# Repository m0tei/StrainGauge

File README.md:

# Strain Gauge Amplifier

A very small analog amplifier board for a full-bridge strain gauge on a carbon rod. It powers the bridge, amplifies the tiny bridge signal by about 151, filters it, and sends one analog voltage to an ADC.

| | |
|---|---|
| Board size | 18.35 × 5.0 mm, 0.8 mm thick, 2 layers |
| Supply | 5 V in, 3.3 V on board |
| Output | Analog, 0.825 V at zero strain |
| Sensitivity | About 0.649 mV/µε at the output |
| Usable range | About 3730 µε compression, 1190 µε extension |
| Bandwidth | About 480 Hz |
| Bridge | 350 Ω full bridge, 3.3 V excitation |
| Design tool | KiCad 10 |

Sensitivity and range assume a gauge factor of 2 and a Poisson ratio of 0.3. Replace these with your gauge and rod values when calibrating.

> **Status:** this is a design that passes KiCad's electrical and layout checks. This repository has no test results from a built board. See [Before ordering](#before-ordering).

## The board

**Top side:** amplifier U2, regulator U1, input filter, and ferrites. The gauge pads J2 are on the left and the cable pads J1 are on the right.

**Bottom side:** VREF buffer U3, VREF divider RN1, gain resistors R1 and R2, output filter R4 and C5, and ESD diodes D1 and D2. This view is flipped, so J2 is on the right.

## How it works

```mermaid
flowchart LR
    A[5 V from J1] --> B[FB1 and D1]
    B --> C[U1 3.3 V regulator]
    C --> D[Strain gauge bridge]
    C --> E[RN1 and U3 make 0.825 V VREF]
    D --> F[Input filter]
    F --> G[U2 amplifier, gain 151]
    E --> G
    G --> H[R4 and C5 output filter]
    H --> I[FB2 and D2]
    I --> J[OUT on J1]
```

### 1. The bridge

Four 350 Ω gauges are bonded to the rod. SG1 and SG3 are axial and sit on opposite sides of the rod. SG2 and SG4 are transverse.

Bending affects the two axial gauges in opposite directions, so it largely cancels. Pure tension or compression adds up. With a 3.3 V supply, the bridge gives about 4.3 µV for each microstrain.

### 2. Power

The 5 V input passes through ferrite FB1, which keeps high-frequency noise out of the regulator. D1 clamps spikes from the cable.

U1 (TPS7A2033) makes the 3.3 V rail. It powers the amplifier and the bridge, and it is also the source for VREF. The bridge draws about 9.4 mA.

### 3. Mid-supply reference

RN1 is a 10k/30k pair that divides 3.3 V by four, and U3 buffers it to make a low-impedance 0.825 V **VREF**. This sets the amplifier's zero point. It sits low because the expected load is lopsided: 3000 µε compression and 300 µε extension. Compression drives the output up, and extension drives it down.

### 4. Input filter

R5, R6, and C6 form a differential low-pass filter with a corner of about 29 kHz, including the bridge resistance. It reduces high-frequency interference picked up on the gauge wires.

### 5. Amplifier

U2 (MCP6N16-100) is a zero-drift instrumentation amplifier. Zero drift means it constantly corrects its own offset, which suits slow, tiny signals like this one.

Two external resistors set the gain:

```
Gain = 1 + R2 / R1 = 1 + 100k / 665 = 151.4
```

The gain depends on the **ratio** of R2 to R1, not their absolute values. R1 is rated ±5 ppm/K and R2 ±10 ppm/K. They come from the same Susumu RG1005 range and sit next to each other, so their ratio stays stable as temperature changes.

The output is:

```
VOUT = VREF + Gain × (SIG+ − SIG−)
```

### 6. Output

R4 and C5 form a low-pass filter at about 480 Hz. This removes noise above the signal band and isolates the amplifier from the cable. FB2 and D2 add high-frequency blocking and ESD protection at the output.

## Wiring

Use the labels printed on the board, because the J2 pad order is not the same as its pin numbers.

**J2, gauge bridge (top to bottom on the board):**

| Label | Pin | Connects to |
|---|---|---|
| EXC+ | 1 | Bridge top, 3.3 V |
| SIG− | 3 | Junction of SG4 and SG3 |
| SIG+ | 2 | Junction of SG1 and SG2 |
| EXC− | 4 | Bridge bottom, GND |

**J1, cable to the ADC (top to bottom on the board):**

| Signal | Pin | Notes |
|---|---|---|
| OUT | 2 | Analog output |
| +5V | 1 | Power input |
| GND | 3 | Ground |

The `OUT 5V GND` silk label is on the back of the board near J2, not beside J1. Follow the table above when wiring J1.

## Reading the output

Convert the voltage to strain with the line below, where compression is positive:

```
strain (µε) = (VOUT − 0.825 V) / 0.000649 V per µε
```

Treat this as a starting point. For real measurements, calibrate the board on the rod with known loads, and measure the zero point at no load.

Both the zero point and the sensitivity follow the 3.3 V rail, and the ADC cannot see that rail through J1. See the first item below.

## Known limitations

- **3.3 V rail drift:** U1 is rated at ±1.5% over temperature. That could move the zero by up to about 12 mV, or roughly 19 µε. This is the largest temperature error in the design.
- **Gauge wires:** J2 has no ESD diodes and no common-mode filter. EXC+ connects directly to the 3.3 V rail.
- **Chopping frequency:** U2 chops at 25 kHz. Strong interference near that frequency, such as from a motor inverter, could mix down into the signal band.
- **ESD diode position:** D1 and D2 sit after the ferrites, and D2 is about 9 mm from J1. Normally they would sit right at the connector.
- **Automotive qualification:** U1 is not AEC-Q100, and the U2 data sheet makes no AEC-Q100 claim.

## Before ordering

- [ ] Confirm R2's AEC-Q200 status and tempco in the Susumu data sheet.
- [ ] Check stock and lead time for R1 and R2. R1 was listed as not stocked at Digi-Key, with a 22-week lead time.
- [ ] Confirm RN1 can be bought. ACASN1002U3002P1AT follows the Vishay part number scheme, but no distributor listing was found. ACASN1002S3002P1AT is listed and has wider ±15 ppm/K tracking.
- [ ] Tell the assembler that RN1 is now polarized. Pin 1 is the GND pad and the 10k side, marked by a dot on the back silkscreen. Fitted backwards, VREF is 2.475 V.
- [ ] Compare U2's land pattern with Microchip's MSOP-8 package drawing. It was adapted from a VSSOP footprint.
- [ ] Check spacing around U1 with your assembler. Parts are close, and the 5 V link beside FB1 is at the 0.127 mm minimum track width.
- [ ] Review the vias at (115.0, 102.72) and (115.0, 104.48), which sit in or at the edge of pads.

## Bill of materials

The full list with manufacturers, ratings, and sources is in [StrainGauge_BOM.csv](StrainGauge_BOM.csv).

| Ref | Part | Purpose |
|---|---|---|
| U1 | TI TPS7A2033PDBVR | 3.3 V regulator |
| U2 | Microchip MCP6N16-100E/MS | Zero-drift instrumentation amplifier |
| U3 | TI OPA388QDBVRQ1 | VREF buffer |
| R1 | Susumu RG1005V-6650-P-T1, 665 Ω | Gain setting |
| R2 | Susumu RG1005N-104-W-T1, 100 kΩ | Gain setting |
| RN1 | Vishay ACASN1002U3002P1AT, 10k/30k | VREF divider |
| R4 | 1 kΩ | Output filter |
| R5, R6 | 100 Ω | Input filter |
| C1, C2 | 1 µF | Regulator input and output |
| C3, C4, C7 | 100 nF | Decoupling and VREF filtering |
| C5 | 330 nF | Output filter |
| C6 | 10 nF | Input filter |
| FB1, FB2 | Murata BLM15PX601SH1D | Connector EMI filtering |
| D1, D2 | TI TPD1E10B06QDPYRQ1 | ESD protection |

## Files

| File | Contents |
|---|---|
| `StrainGauge.kicad_pro` | KiCad project, open this first |
| `StrainGauge.kicad_sch` | Schematic |
| `StrainGauge.kicad_pcb` | PCB layout |
| `StrainGauge.kicad_sym` | Project symbols |
| `StrainGauge.pretty/` | Project footprints |
| `StrainGauge_BOM.csv` | Bill of materials |
| `StrainGauge_top.png`, `StrainGauge_bottom.png` | Board renders |
| `docs/` | Schematic images used in this README |

## Data sheets

- [MCP6N16 amplifier](https://ww1.microchip.com/downloads/en/DeviceDoc/20005318A.pdf)
- [TPS7A20 regulator](https://www.ti.com/lit/ds/symlink/tps7a20.pdf)
- [ACAS resistor arrays](https://www.vishay.com/doc?28770)

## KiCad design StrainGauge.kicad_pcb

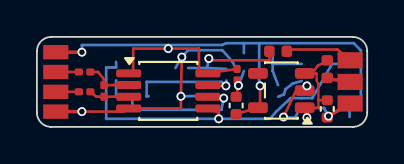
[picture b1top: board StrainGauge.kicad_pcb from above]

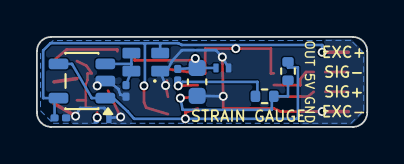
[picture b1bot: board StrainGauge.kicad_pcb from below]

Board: 2 copper layers, 18.3 x 5.0 mm, 22 parts (10 on the bottom side), 14 nets.

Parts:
C1, C2: 1u 10V; C_0402_1005Metric
C3, C4, C7: 100n 10V; C_0201_0603Metric
C5: 330n 16V; C_0603_1608Metric
C6: 10n 10V; C_0201_0603Metric
D1, D2: ESD 5.5V; TVS_X1SON-2_DPY
FB1, FB2: 600R; L_0402_1005Metric
J1: To ADC / 5 V; CablePads_1x03
J2: To rod; GaugePads_1x04
R1: 665R 0.02%; R_0402_1005Metric
R2: 100k 0.05%; R_0402_1005Metric
R4: 1k; R_0201_0603Metric
R5, R6: 100R; R_0201_0603Metric
RN1: 10k/30k; ACAS_0606
U1: TPS7A2033PDBVR; TI_DBV0005A_SOT-23-5
U2: MCP6N16-100E/MS; Microchip_MS_MSOP-8
U3: OPA388QDBVRQ1; TI_DBV0005A_SOT-23-5

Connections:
+3V3: C2.1, C3.1, C7.1, J2.1, RN1.2, U1.5 (OUT), U2.1, U2.8, U3.5
+5V: C1.1, D1.2, FB1.1, U1.1 (IN), U1.3 (EN)
/OUT: C5.1, D2.2, FB2.1, R4.2
/OUT_J1: FB2.2, J1.2
/SIG+: J2.2, R5.1
/SIG-: J2.3, R6.1
/VDIV: C4.1, RN1.3, RN1.4, U3.3
/VFG: R1.1, R2.2, U2.6
/VIN_J1: FB1.2, J1.1
/VO: R2.1, R4.1, U2.7
/VREF: R1.2, U2.5, U3.1, U3.4
GND: C1.2, C2.2, C3.2, C4.2, C5.2, C7.2, D1.1, D2.1, J1.3, J2.4, RN1.1, U1.2 (GND), U2.4, U3.2
unnamed: C6.2, R6.2, U2.2
unnamed: C6.1, R5.2, U2.3

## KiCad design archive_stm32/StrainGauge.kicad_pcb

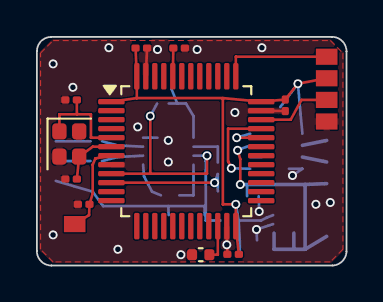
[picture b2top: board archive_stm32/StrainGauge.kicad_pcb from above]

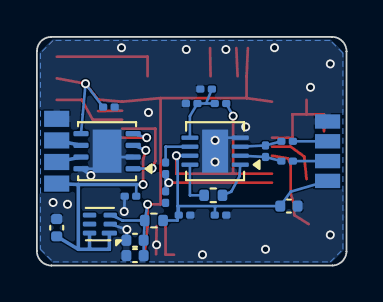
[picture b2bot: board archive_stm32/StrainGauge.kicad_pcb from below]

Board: 2 copper layers, 17.2 x 12.7 mm, 34 parts (23 on the bottom side), 24 nets.

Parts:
C1, C2, C7: 1u 10V; C_0402_1005Metric
C3, C4, C8, C10, C11, C12, C16, C17, C20: 100n; C_0201_0603Metric
C5: 330n; C_0201_0603Metric
C6: 10n; C_0201_0603Metric
C13, C14: 4.7u 10V; C_0402_1005Metric
C18, C19: 10p; C_0201_0603Metric
FB1: 600R 100MHz; R_0402_1005Metric
J1: 5 V / CAN; BusPads_1x04
J2: To rod; GaugePads_1x04
J3: SWD; DebugPads_1x05
R1: 499R 0.1%; R_0402_1005Metric
R2, R3, R4: 1k; R_0201_0603Metric
R5, R6: 100R; R_0201_0603Metric
R7: 10k; R_0201_0603Metric
U1: TLV70033DSE; WSON-6_1.5x1.5mm_P0.5mm
U2: INA333xxDRG; WSON-8-1EP_3x3mm_P0.5mm_EP1.45x2.4mm
U3: STM32U575CIT6; LQFP-48_7x7mm_P0.5mm
U4: TJA1441ATK; HVSON-8-1EP_3x3mm_P0.65mm_EP1.6x2.4mm
Y1: 16 MHz; Crystal_SMD_2016-4Pin_2.0x1.6mm

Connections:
+3.3VA: C3.1, C7.1, C8.1, FB1.2, J2.1, R2.1, U2.7, U3.9
+3V3: C2.1, C10.1, C11.1, C12.1, C13.1, C17.1, FB1.1, J3.1, U1.3, U3.1, U3.24, U3.36, U3.48, U4.5
+5V: C1.1, C16.1, J1.1, U1.1, U1.6, U4.3
/AMP_OUT: C5.1, R4.2, U3.10
/BOOT0: R7.1, U3.44
/CANH: J1.2, U4.7
/CANL: J1.3, U4.6
/CAN_RX: U3.32, U4.4
/CAN_TX: U3.33, U4.1
/HSE_IN: C18.1, U3.5, Y1.1
/HSE_OUT: C19.1, U3.6, Y1.3
/NRST: C20.1, J3.4, U3.7
/SIG+: J2.2, R5.1
/SIG-: J2.3, R6.1
/SWCLK: J3.3, U3.37
/SWDIO: J3.2, U3.34
/VCAP: C14.1, U3.22
/VREF: C4.1, R2.2, R3.1, U2.5
GND: C1.2, C2.2, C3.2, C4.2, C5.2, C7.2, C8.2, C10.2, C11.2, C12.2, C13.2, C14.2, C16.2, C17.2, C18.2, C19.2, C20.2, J1.4, J2.4, J3.5, R3.2, R7.2, U1.2, U2.4, U2.9, U3.8, U3.23, U3.35, U3.47, U4.2, U4.8, U4.9, Y1.2, Y1.4
unnamed: R1.1, U2.1
unnamed: R1.2, U2.8
unnamed: R4.1, U2.6
unnamed: C6.1, R5.2, U2.3
unnamed: C6.2, R6.2, U2.2
